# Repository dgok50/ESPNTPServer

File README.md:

# ESPNTPServer

GPS-synchronized ESP8266 time server with legacy time protocols and NMEA output.

The current debug build is `1.3.7-debug`. See [the protocol reference](docs/PROTOCOLS.md)
for wire formats, availability rules, discovery, management routes, and tests.

## Features

| Interface | Transport | Purpose |
| --- | --- | --- |
| NTP v3/v4 | UDP 123 | GPS/PPS-synchronized stratum-1 time |
| RFC 867 Daytime | TCP and UDP 13 | Human-readable UTC time |
| RFC 868 Time | TCP and UDP 37 | Four-byte 1900-epoch time |
| NMEA 0183 | TCP 10110 | GGA/RMC stream for local clients |
| NMEA 0183 | UDP 10110 | GGA/RMC directed-subnet broadcast |
| mDNS/DNS-SD | UDP 5353 | Discover HTTP and NMEA services |
| Management | HTTP on TCP 80 | Diagnostics and controlled OTA reboot |
| Receiver control, debug only | HTTP on TCP 80 | Bidirectional UBX request/response |

The device also reads NMEA/UBX from the receiver over UART and PPS on GPIO12,
downloads firmware from its configured HTTP(S) OTA server at boot, and can send
optional UDP syslog to a configured host. These are not additional public
time-service listeners. The temporary Wi-Fi configuration portal is separate
from the normal management API. Details are in the [protocol reference](docs/PROTOCOLS.md).

All time protocols use the GPS time source for high accuracy. There is no
fixed startup or recovery delay: they become available on the first PPS edge
after valid GNSS input and confirmed UTC time from RMC. They become silent
again when GNSS input or PPS is lost. Network NMEA has its own fix filter.

The GPS PPS signal on GPIO12/D6 is captured by a minimal IRAM interrupt
handler. NTP uses the raw lwIP UDP API so receive and transmit timestamps are
placed as close as the ESP8266 software stack permits to packet processing.
The ESP8266 Wi-Fi hardware does not provide MAC-level packet timestamps, so
radio scheduling and retransmissions can still add millisecond-scale jitter.
The NTP root-dispersion value therefore has a conservative five-millisecond
software-timestamp uncertainty floor. This describes server-side uncertainty;
clients still measure and filter their own network round-trip delay.

## Network NMEA

The server publishes an `ESPNTP NMEA` DNS-SD service with `accuracy=exact` and
streams CRLF-terminated NMEA 0183 GGA and RMC sentences to persistent TCP
clients on the IANA-assigned port 10110. It also sends each sentence as one UDP
datagram to the directed broadcast address of the local subnet on port 10110
and advertises `ESPNTP NMEA Broadcast` as `_nmea-0183._udp.local`. Only
sentences with a valid NMEA checksum and a usable position fix are forwarded.
The TCP service and management interface accept clients only from the device's
local IP subnet; the UDP datagrams remain confined to that subnet by broadcast
routing rules.

NMEA transmission and mDNS processing run in the latter half of each PPS
second, keeping this background traffic away from the PPS edge and the most
latency-sensitive NTP receive/transmit window. UDP uses the asynchronous lwIP
path: the firmware only copies a small datagram into the network stack and
never waits for a receiver or acknowledgement. The fixed queue and two-client
TCP limit bound RAM use and disconnect persistently slow TCP clients.

OpenCPN, AvNav, gpsd, Signal K/OpenPlotter and many marine navigation apps can
receive NMEA 0183 over UDP. Configure a UDP input on port 10110; no sender IP is
needed for broadcast reception. TCP remains preferable when delivery and order
must be guaranteed. Plain NMEA 0183 multicast is deliberately not enabled:
there is no universally assigned multicast group and it is less widely
supported than broadcast. IEC 61162-450 and NMEA OneNet multicast are different
protocols and are not advertised by this firmware.

## HTTP diagnostics and OTA

The management interface listens on TCP port 80 and only accepts requests from
the device's local IP subnet.

- `GET /diagnostics.txt` returns plain-text `key=value` runtime diagnostics,
  including PPS age, PPS timeout count, GPS validity count, and protocol
  request/response counters. It also reports the NTP timestamp mode,
  advertised timestamp uncertainty, and latest/maximum response-processing
  times.
- In the temporary debug build, diagnostics also show the latest receiver
  `MON-HW` interference state, its age, CW indicator, noise, AGC, and antenna
  supervisor status. The receiver pushes `MON-HW` over UART1 every 10 seconds;
  an HTTP request does not poll the receiver. State `unknown` is not equivalent
  to `ok`.
- The experimental debug build also caches sparse `NAV-PVT`, `NAV-DOP`,
  `NAV-SVINFO`, and `MON-IO` messages. Diagnostics show fix validity/type,
  satellites used, time/horizontal accuracy, DOP, GPS signal/ephemeris/C/N0
  aggregates, and UART1 error counters. `MON-HW` additionally supplies event
  transition counts, last-event time, and a minute-bucket maximum `jamInd` over
  the last hour. These are receiver estimates and counters, not NTP network
  timestamp accuracy; absent or stale messages must not be treated as healthy.
- `POST /ota` schedules a reboot and therefore an immediate OTA check during
  startup. The request must contain `X-OTA-Confirm: reboot`; the custom header
  also prevents a normal cross-origin browser form from triggering a reboot.
- The temporary `1.3.7-debug` build exposes `POST /debug/ubx` and
  `GET /debug/ubx` for arbitrary checked UBX frames and matching responses.
  It has no password or HTTPS and is restricted only to the device's local
  subnet. Do not use this image on an untrusted network.

Examples:

```sh
curl 'http://<device-ip>/diagnostics.txt'
curl -X POST -H 'X-OTA-Confirm: reboot' 'http://<device-ip>/ota'
```

Replace `<device-ip>` with the unit's address on your local subnet.

OTA runs before the GPS PPS interrupt is enabled, including after a remotely
requested reboot.

## CI/CD

GitLab CI validates and builds commits unless CI is explicitly skipped (for
example, with `[skip ci]`). Pipelines on the default branch (`master`)
additionally publish `firmware.bin` to the configured OTA directory. The
deployment target, verification route, host key, and firmware defaults are
provided by protected CI variables, not stored in this repository. Deployment
verifies the image size, MD5, and SHA-256 before
publication, preserves the previous image, replaces the active file atomically,
and downloads it through the real OTA endpoint as a final end-to-end check. A
failed final check restores the previous firmware.

## Contents

[src](src) Contains the code for the NTP Server

[eagle](eagle) contains the schematic and board designs in Eagle cad.

[enclosure](enclosure) contains the STL files for the enclosure.

This is designed around [this GPS module](https://www.amazon.com/gp/product/B075DD5746/) but any module with standard NMEA output and a pult per second signal will work if you redesign the board or use an adapter.

I also used [this display module](https://www.amazon.com/gp/product/B00O2KDQBE/).  You can use others but be careful with the power polarity, I have modules where VCC and ground pins are in a different order.

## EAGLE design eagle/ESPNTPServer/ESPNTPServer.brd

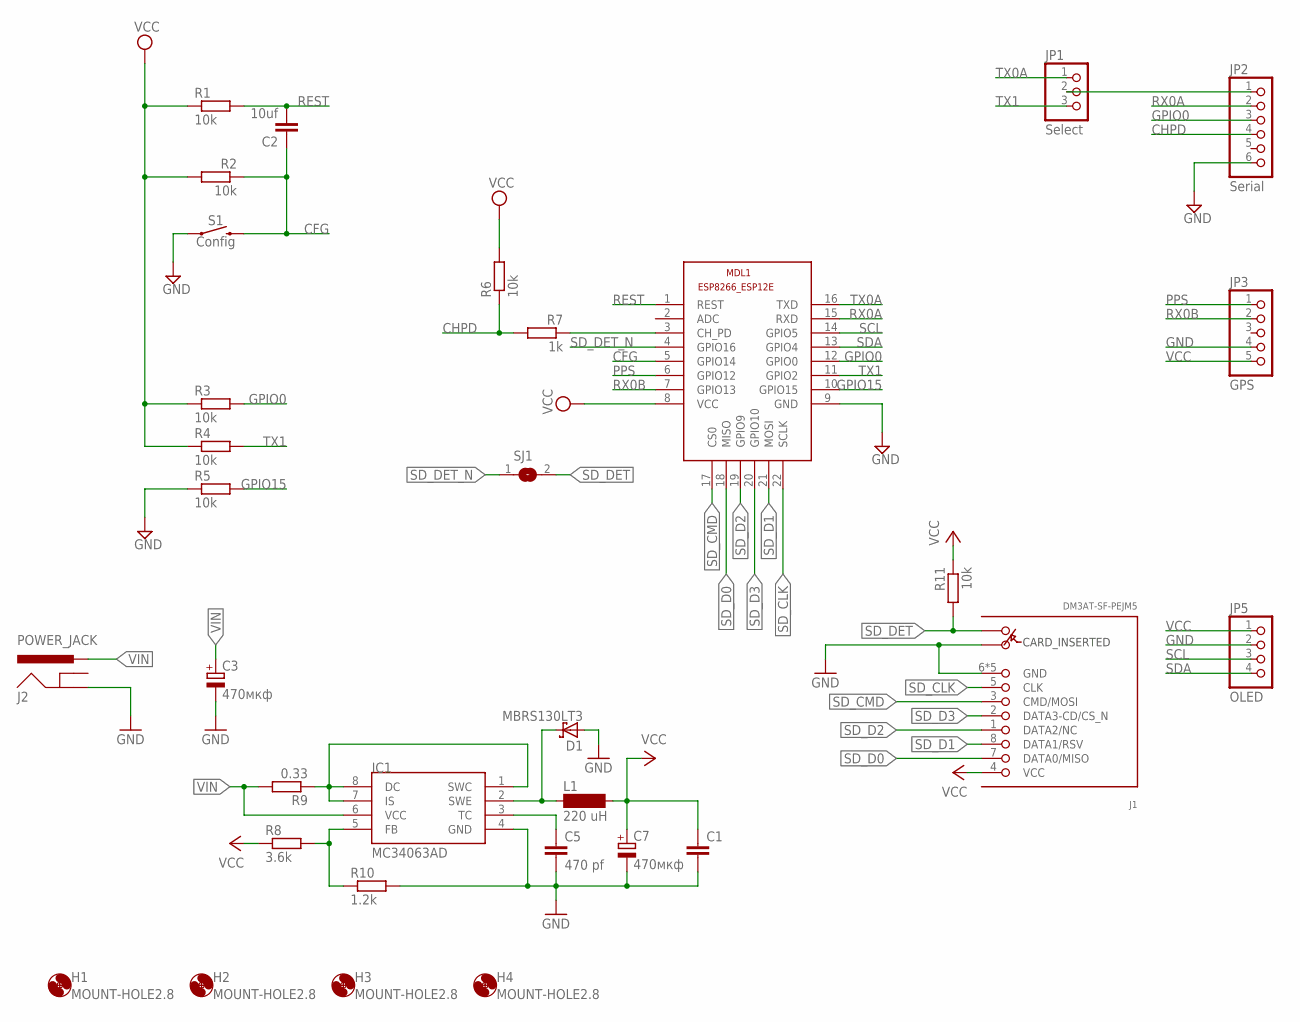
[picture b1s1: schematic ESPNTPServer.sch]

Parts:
C1: C-EUC1206; C1206
C2: 10uf; C050-025X075
C3, C7: 470мкф; E3,5-8
C5: 470 pf; C1206
D1: MBRS130LT3; SMB
H1, H2, H3, H4: MOUNT-HOLE2.8; 2,8
IC1: MC34063AD; SOIC8
J1: DM3AT-SF-PEJM5
J2: POWER_JACK; POWER_JACK_PTH
JP1: Select; 1X03
JP2: Serial; 1X06
JP3: GPS; 1X05
JP5: OLED; 1X04
L1: 220 uH; SD12K-82
MDL1: ESP8266-12F; ESP8266-ESP12E
R1, R2, R3, R4, R5, R6, R11: 10k; M1206
R7: 1k; M1206
R8: 3.6k; M1206
R9: 0.33; 0411V
R10: 1.2k; M1206
S1: Config; TACTILE_SWITCH_PTH_6.0MM
SJ1: SJ

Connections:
CFG: C2.1, MDL1.5 (GPIO14), R2.1, S1.3 (2)
CHPD: JP2.4, R6.1, R7.2
GND: C1.2, C3.-, C5.2, C7.-, D1.A, IC1.4 (GND), J1.6 (GND), J1.A, J1.MOUNT0 (GND), J1.MOUNT1 (GND), J1.MOUNT2 (GND), J1.MOUNT3 (GND), J2.GND, JP2.6, JP3.4, JP5.2, MDL1.9 (GND), R5.1, R10.2, S1.1
GPIO0: JP2.3, MDL1.12 (GPIO0), R3.2
GPIO15: MDL1.10 (GPIO15), R5.2
unnamed: JP1.2, JP2.1
unnamed: IC1.1 (SWC), IC1.7 (IS), IC1.8 (DC), R9.1
unnamed: C5.1, IC1.3 (TC)
unnamed: MDL1.3 (CH_PD), R7.1
unnamed: D1.C, IC1.2 (SWE), L1.1
unnamed: IC1.5 (FB), R8.2, R10.1
PPS: JP3.1, MDL1.6 (GPIO12)
REST: C2.2, MDL1.1 (REST), R1.2
RX0A: JP2.2, MDL1.15 (RXD)
RX0B: JP3.2, MDL1.7 (GPIO13)
SCL: JP5.3, MDL1.14 (GPIO5)
SDA: JP5.4, MDL1.13 (GPIO4)
SD_CLK: J1.5 (CLK), MDL1.22 (SCLK)
SD_CMD: J1.3 (CMD/MOSI), MDL1.17 (CS0)
SD_D0: J1.7 (DATA0/MISO), MDL1.18 (MISO)
SD_D1: J1.8 (DATA1/RSV), MDL1.21 (MOSI)
SD_D2: J1.1 (DATA2/NC), MDL1.19 (GPIO9)
SD_D3: J1.2 (DATA3-CD/CS_N), MDL1.20 (GPIO10)
SD_DET: J1.B, R11.2, SJ1.2
SD_DET_N: MDL1.4 (GPIO16), SJ1.1
TX0A: JP1.1, MDL1.16 (TXD)
TX1: JP1.3, MDL1.11 (GPIO2), R4.2
VCC: C1.1, C7.+, J1.4 (VCC), JP3.5, JP5.1, L1.2, MDL1.8 (VCC), R1.1, R2.2, R3.1, R4.1, R6.2, R8.1, R11.1
VIN: C3.+, IC1.6 (VCC), J2.PWR, R9.2

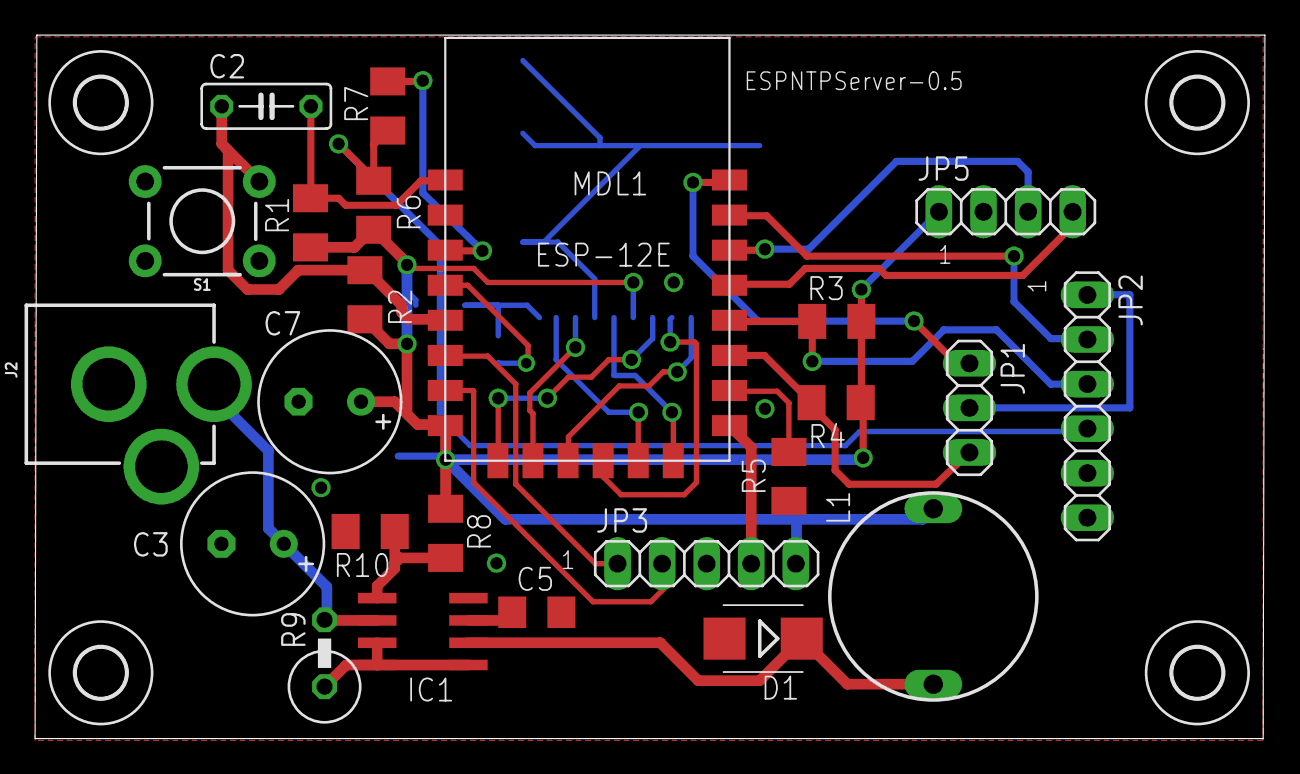
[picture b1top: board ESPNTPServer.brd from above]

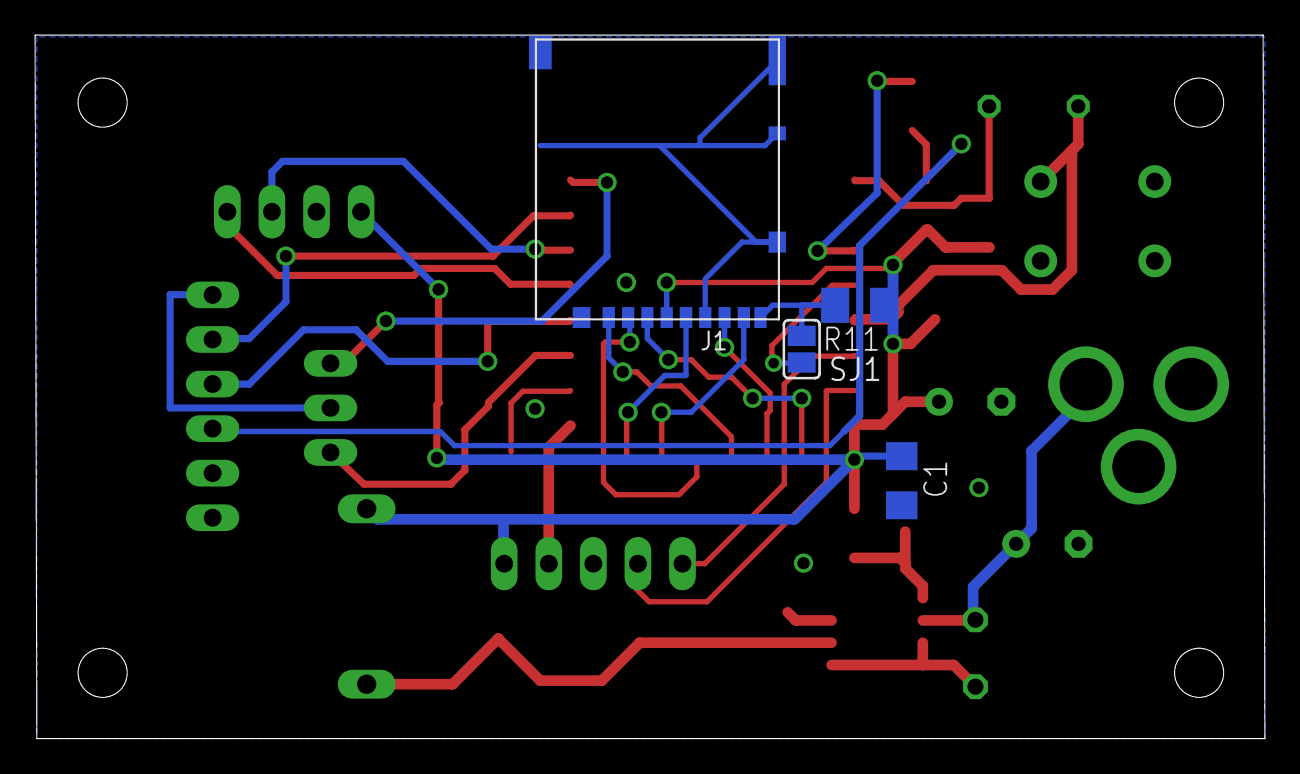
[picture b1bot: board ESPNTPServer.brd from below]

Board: 2 copper layers, 70.1 x 40.1 mm, 32 parts (4 on the bottom side), 29 nets.

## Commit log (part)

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2020-03-14 Change power supply from linar to Switch
2020-03-14 Some fixes
2020-03-14 Update image
2026-01-10 Initial plan
2026-01-10 Implement legacy time protocols support (RFC 867 and RFC 868)
2026-01-10 Update README to document legacy time protocol support
2026-01-10 Add _codeql_detected_source_root to .gitignore
